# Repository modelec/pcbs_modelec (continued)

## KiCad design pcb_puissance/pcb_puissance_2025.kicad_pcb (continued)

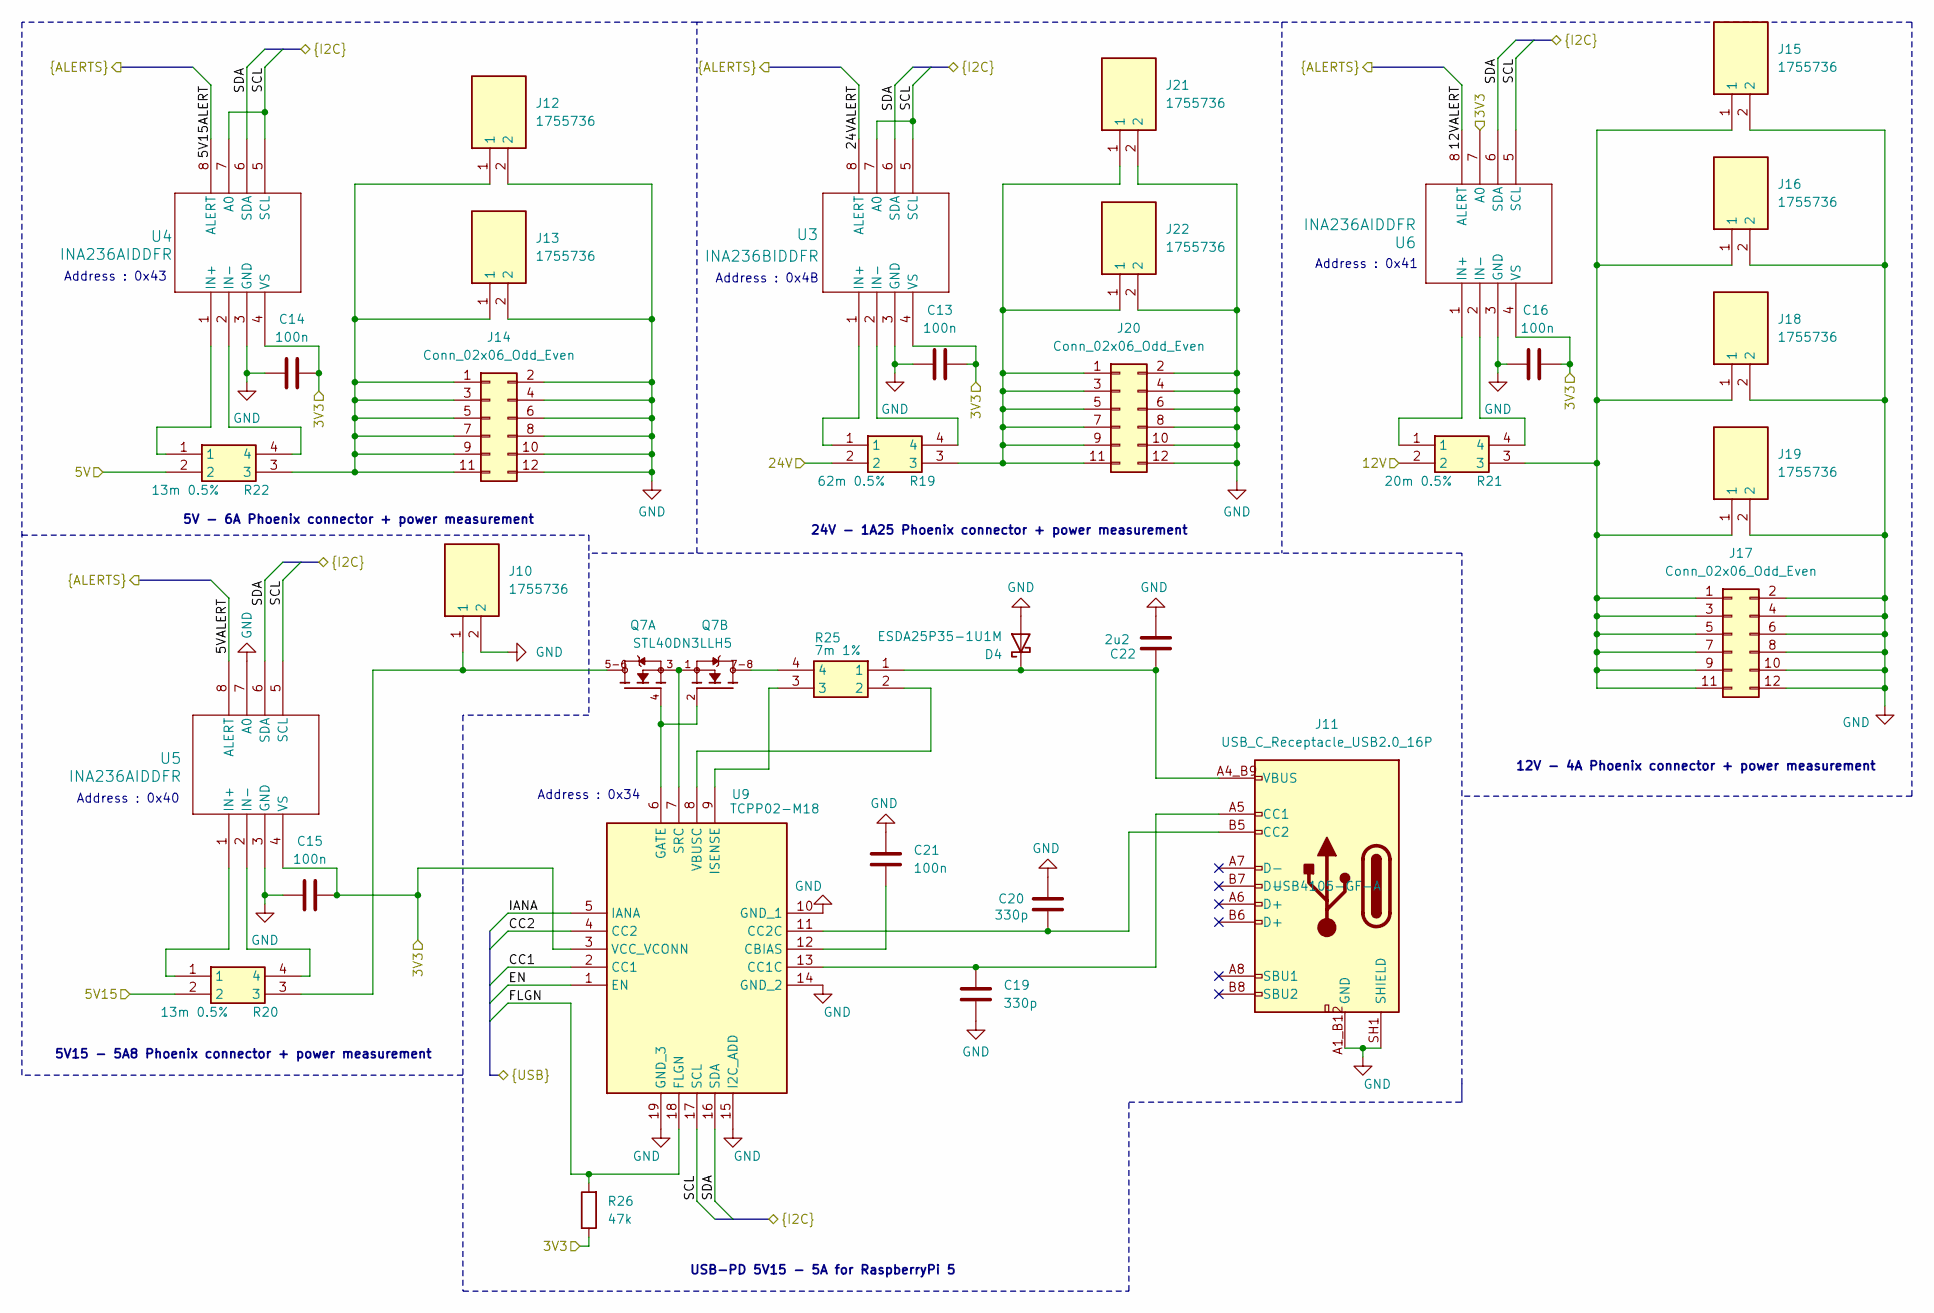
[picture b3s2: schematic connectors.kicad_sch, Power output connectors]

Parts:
C13, C14, C15, C16, C21: 100n; C_0805_2012Metric_Pad1.18x1.45mm_HandSolder; Manufacturer_Part_Number VJ0805Y104KXAMR
C19, C20: 330p; C_0805_2012Metric_Pad1.18x1.45mm_HandSolder; Manufacturer_Part_Number VJ0805A331FXACW1BC
C22: 2u2; C_0805_2012Metric_Pad1.18x1.45mm_HandSolder; Manufacturer_Part_Number VJ0805G225KXQTW1BC
D4: ESDA25P35-1U1M; QFN1610_STM; Manufacturer_Part_Number ESDA25P35-1U1M
J10, J12, J13, J15, J16, J18, J19, J21, J22: 1755736; PhoenixContact_MSTBVA_2,5_2-G-5,08_1x02_P5.08mm_Vertical; Manufacturer_Part_Number 1755736; Mouser Part Number 651-1755736
J11: USB_C_Receptacle_USB2.0_16P; GCT_USB4105-GF-A; Manufacturer_Part_Number USB4105-GF-A
J14, J17, J20: Conn_02x06_Odd_Even; PinHeader_2x06_P1.27mm_Vertical
Q7: STL40DN3LLH5; TRANS_STL40DN3LLH5; PARTREV 7
R19: 62m 0.5%; L4CL1206LR013DNR; Manufacturer_Part_Number L4CL1206LR062DNR
R20, R22: 13m 0.5%; L4CL1206LR013DNR; Manufacturer_Part_Number L4CL1206LR013DNR
R21: 20m 0.5%; L4CL1206LR013DNR; Manufacturer_Part_Number L4CL1206LR020DNR
R25: 7m 1%; L4CL1206LR013DNR; Manufacturer_Part_Number L4CL1206LR007FNR
R26: 47k; R_0805_2012Metric_Pad1.20x1.40mm_HandSolder; Manufacturer_Part_Number CRCW080547K0FKEA
U3: INA236BIDDFR; SOT23-8_DDF_TEX; Manufacturer_Part_Number INA236BIDDFR
U4, U5, U6: INA236AIDDFR; SOT23-8_DDF_TEX; Manufacturer_Part_Number INA236AIDDFR
U9: TCPP02-M18; QFN50P350X350X60-19N-D; Mouser Part Number 511-TCPP02-M18

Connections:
/3V3: C13.2, C14.2, C15.2, C16.2, R26.1, U3.4 (VS), U4.4 (VS), U5.4 (VS), U6.4 (VS), U6.7 (A0), U9.3 (VCC_VCONN); also elsewhere on the board
/Converters/5V: R22.2; also elsewhere on the board
/Converters/5V15: R20.2; also elsewhere on the board
/Converters/12V: R21.2; also elsewhere on the board
/Converters/24V: R19.2; also elsewhere on the board
/Microcontroller/12VALERT: U3.8 (ALERT), U4.8 (ALERT), U5.8 (ALERT), U6.8 (ALERT); also elsewhere on the board
/Microcontroller/CC1: U9.2 (CC1); also elsewhere on the board
/Microcontroller/CC2: U9.4 (CC2); also elsewhere on the board
/Microcontroller/EN: U9.1 (EN)
/Microcontroller/FLGN: R26.2, U9.18 (FLGN); also elsewhere on the board
/Microcontroller/IANA: U9.5 (IANA)
/Microcontroller/SCL: U3.5 (SCL), U3.7 (A0), U4.5 (SCL), U4.7 (A0), U5.5 (SCL), U6.5 (SCL), U9.17 (SCL); also elsewhere on the board
/Microcontroller/SDA: U3.6 (SDA), U4.6 (SDA), U5.6 (SDA), U6.6 (SDA), U9.16 (SDA); also elsewhere on the board
GND: C13.1, C14.1, C15.1, C16.1, C19.2, C20.1, C21.1, C22.2, D4.2 (A), J10.2, J11.A1_B12 (GND), J11.B1_A12 (GND), J11.SH1 (SHIELD), J11.SH2, J11.SH3, J11.SH4, J12.2, J13.2, J14.2, J14.4, J14.6, J14.8, J14.10, J14.12, J15.2, J16.2, J17.2, J17.4, J17.6, J17.8, J17.10, J17.12, J18.2, J19.2, J20.2, J20.4, J20.6, J20.8, J20.10, J20.12, J21.2, J22.2, U3.3 (GND), U4.3 (GND), U5.3 (GND), U5.7 (A0), U6.3 (GND), U9.10 (GND_1), U9.14 (GND_2), U9.15 (I2C_ADD), U9.19 (GND_3); also elsewhere on the board
unnamed: C22.1, D4.1 (K), J11.A4_B9 (VBUS), J11.B4_A9 (VBUS), R25.1
unnamed: J10.1, Q7.5-6, R20.3
unnamed: C19.1, J11.A5 (CC1), U9.13 (CC1C)
unnamed: C20.2, J11.B5 (CC2), U9.11 (CC2C)
unnamed: J12.1, J13.1, J14.1, J14.3, J14.5, J14.7, J14.9, J14.11, R22.3
unnamed: J15.1, J16.1, J17.1, J17.3, J17.5, J17.7, J17.9, J17.11, J18.1, J19.1, R21.3
unnamed: J20.1, J20.3, J20.5, J20.7, J20.9, J20.11, J21.1, J22.1, R19.3
unnamed: Q7.7-8, R25.4
unnamed: R19.1, U3.1 (IN+)
unnamed: R19.4, U3.2 (IN-)
unnamed: R22.1, U4.1 (IN+)
unnamed: R22.4, U4.2 (IN-)
unnamed: R20.1, U5.1 (IN+)
unnamed: R20.4, U5.2 (IN-)
unnamed: R21.1, U6.1 (IN+)
unnamed: R21.4, U6.2 (IN-)
unnamed: C21.2, U9.12 (CBIAS)
unnamed: Q7.2, Q7.4, U9.6 (GATE)
unnamed: R25.3, U9.9 (ISENSE)
unnamed: Q7.1, Q7.3, U9.7 (SRC)
unnamed: R25.2, U9.8 (VBUSC)

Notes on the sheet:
Address : 0x41
5V15 - 5A8 Phoenix connector + power measurement
5V - 6A Phoenix connector + power measurement
Address : 0x43
USB-PD 5V15 - 5A for RaspberryPi 5
Address : 0x34
Address : 0x4B
24V - 1A25 Phoenix connector + power measurement
12V - 4A Phoenix connector + power measurement
Address : 0x40

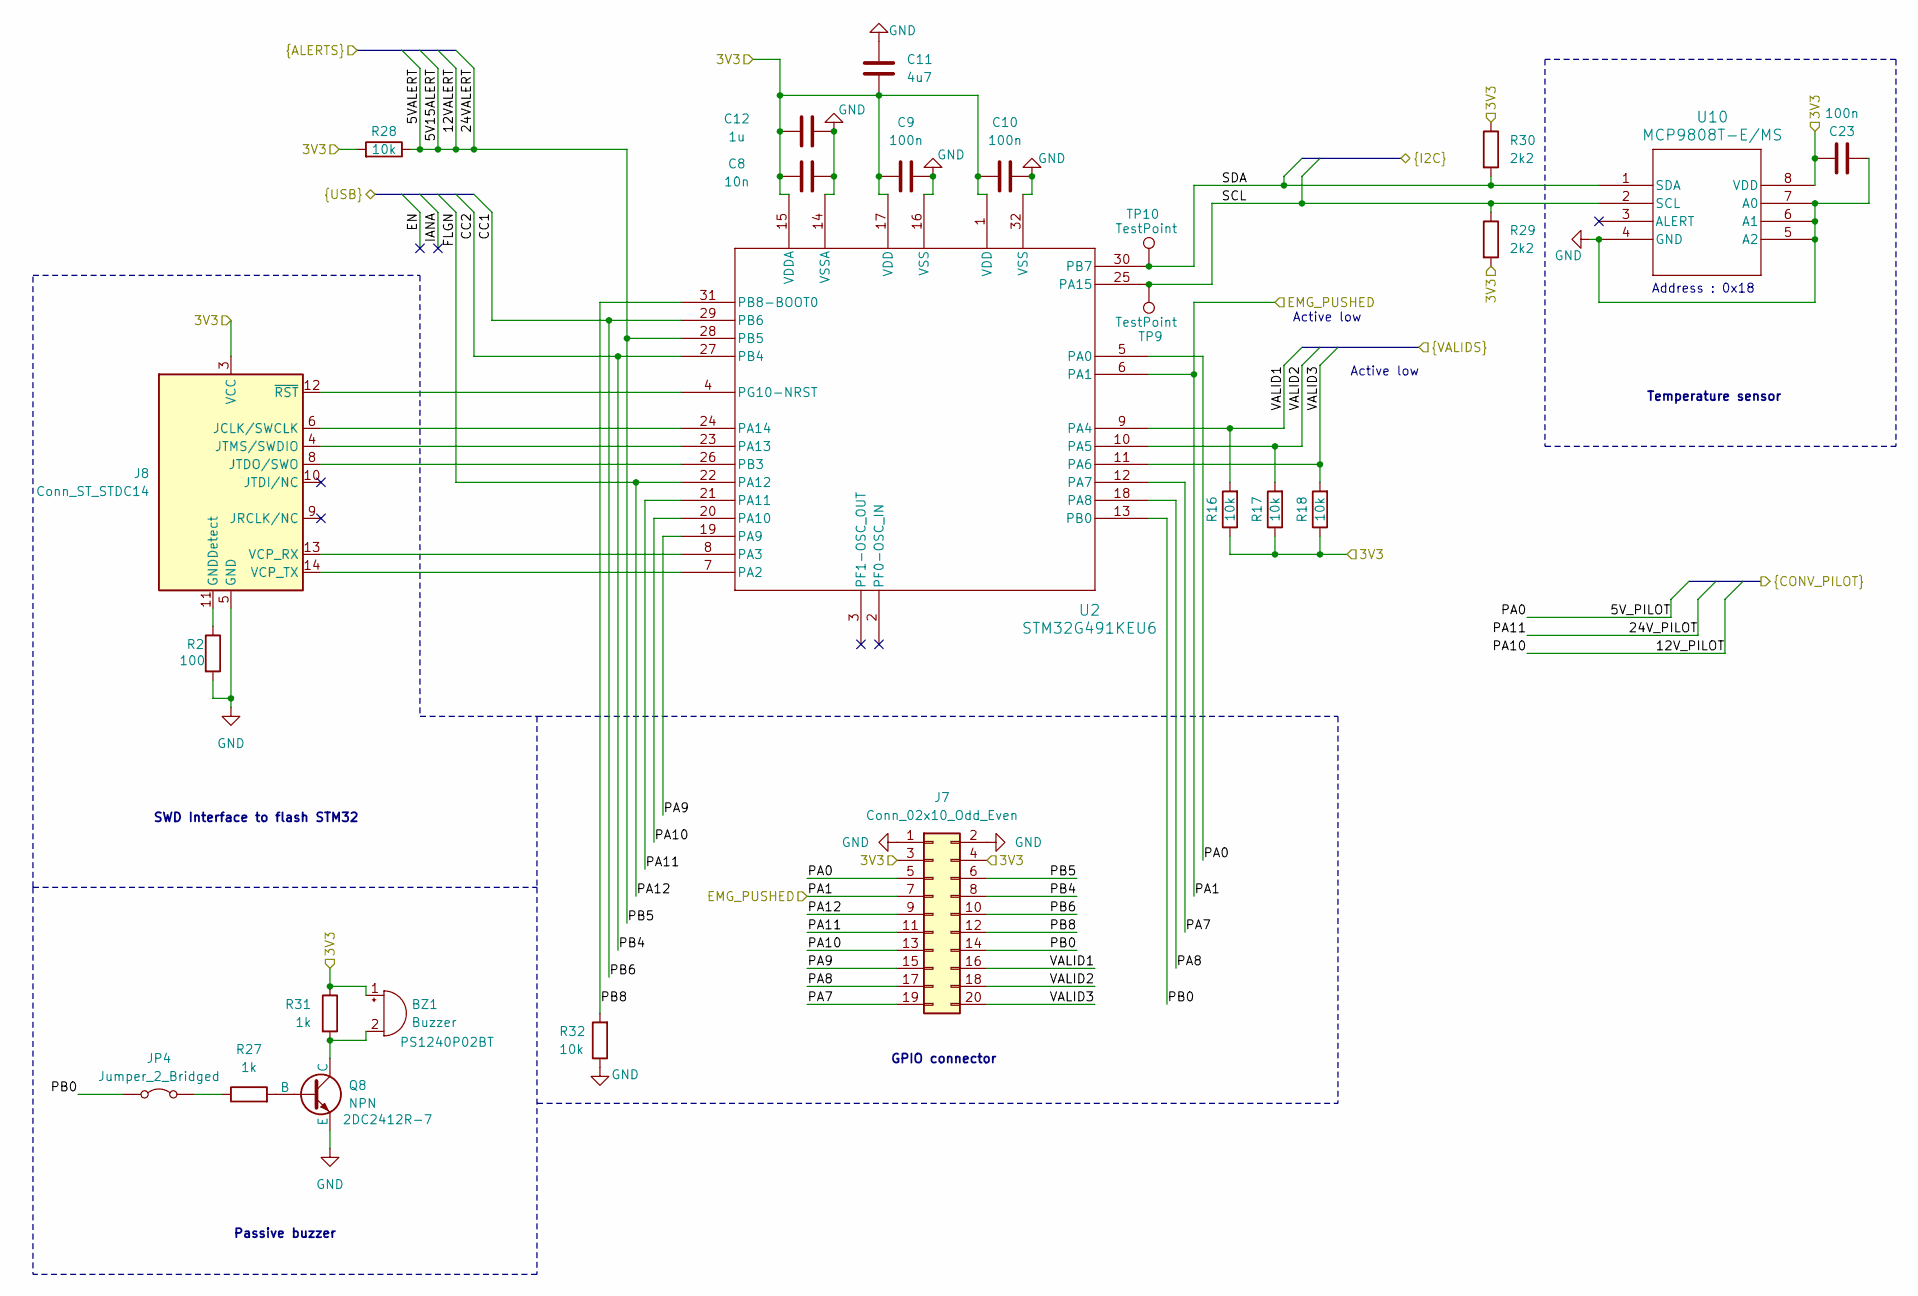
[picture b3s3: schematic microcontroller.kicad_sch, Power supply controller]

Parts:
BZ1: Buzzer; XTAL_PS1240P02BT_TDK; Manufacturer_Part_Number PS1240P02BT
C8: 10n; C_0805_2012Metric_Pad1.18x1.45mm_HandSolder; Manufacturer_Part_Number VJ0805Y103KXAMC
C9, C10, C23: 100n; C_0805_2012Metric_Pad1.18x1.45mm_HandSolder; Manufacturer_Part_Number VJ0805Y104KXAMR
C11: 4u7; C_0805_2012Metric_Pad1.18x1.45mm_HandSolder; Manufacturer_Part_Number VJ0805G475KXQTW1BC
C12: 1u; C_0805_2012Metric_Pad1.18x1.45mm_HandSolder; Manufacturer_Part_Number VJ0805Y105KXQTW1BC
J7: Conn_02x10_Odd_Even; PinHeader_2x10_P1.27mm_Vertical
J8: Conn_ST_STDC14; PinHeader_2x07_P1.27mm_Vertical; Manufacturer_Part_Number 3220-14-0100-00
JP4: Jumper_2_Bridged; PinHeader_1x02_P1.27mm_Vertical
Q8: NPN; SOT-23; Manufacturer_Part_Number 2DC2412R-7
R2: 100; R_0805_2012Metric_Pad1.20x1.40mm_HandSolder; Manufacturer_Part_Number CRCW0805100RFKEA
R16, R17, R18, R28, R32: 10k; R_0805_2012Metric_Pad1.20x1.40mm_HandSolder; Manufacturer_Part_Number CRCW080510K0FKEA
R27, R31: 1k; R_0805_2012Metric_Pad1.20x1.40mm_HandSolder; Manufacturer_Part_Number CRCW08051K00FKEA
R29, R30: 2k2; R_0805_2012Metric_Pad1.20x1.40mm_HandSolder; Manufacturer_Part_Number CRCW08052K20FKEA
TP9, TP10: TestPoint; TestPoint_Bridge_Pitch2.0mm_Drill0.7mm
U2: STM32G491KEU6
U10: MCP9808T-E/MS; MSOP8_MC_MCH; Manufacturer_Part_Number MCP9808T-E/MS

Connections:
/3V3: BZ1.1 (+), C8.1, C9.1, C10.1, C11.1, C12.1, C23.2, J7.3, J7.4, J8.3 (VCC), R16.1, R17.1, R18.1, R28.2, R29.2, R30.1, R31.1, U2.1 (VDD), U2.15 (VDDA), U2.17 (VDD), U10.8 (VDD); also elsewhere on the board
/Converters/5V_PILOT: J7.5, U2.5 (PA0); also elsewhere on the board
/Converters/12V_PILOT: J7.13, U2.20 (PA10); also elsewhere on the board
/Converters/24V_PILOT: J7.11, U2.21 (PA11); also elsewhere on the board
/Microcontroller/12VALERT: J7.6, R28.1, U2.28 (PB5); also elsewhere on the board
/Microcontroller/CC1: J7.10, U2.29 (PB6); also elsewhere on the board
/Microcontroller/CC2: J7.8, U2.27 (PB4); also elsewhere on the board
/Microcontroller/FLGN: J7.9, U2.22 (PA12); also elsewhere on the board
/Microcontroller/PA1: J7.7, U2.6 (PA1); also elsewhere on the board
/Microcontroller/PA7: J7.19, U2.12 (PA7)
/Microcontroller/PA8: J7.17, U2.18 (PA8)
/Microcontroller/PA9: J7.15, U2.19 (PA9)
/Microcontroller/PB0: J7.14, JP4.1 (A), U2.13 (PB0)
/Microcontroller/PB8: J7.12, R32.2, U2.31 (PB8-BOOT0)
/Microcontroller/SCL: R29.1, TP9.1, U2.25 (PA15), U10.2 (SCL); also elsewhere on the board
/Microcontroller/SDA: R30.2, TP10.1, U2.30 (PB7), U10.1 (SDA); also elsewhere on the board
/Microcontroller/VALID1: J7.16, R16.2, U2.9 (PA4); also elsewhere on the board
/Microcontroller/VALID2: J7.18, R17.2, U2.10 (PA5); also elsewhere on the board
/Microcontroller/VALID3: J7.20, R18.2, U2.11 (PA6); also elsewhere on the board
GND: C8.2, C9.2, C10.2, C11.2, C12.2, C23.1, J7.1, J7.2, J8.5 (GND), J8.7 (GND), Q8.1 (E), R2.2, R32.1, U2.14 (VSSA), U2.16 (VSS), U2.32 (VSS), U10.4 (GND), U10.5 (A2), U10.6 (A1), U10.7 (A0); also elsewhere on the board
unnamed: BZ1.2 (-), Q8.3 (C), R31.2
unnamed: J8.11 (GNDDetect), R2.1
unnamed: J8.6 (JCLK/SWCLK), U2.24 (PA14)
unnamed: J8.8 (JTDO/SWO), U2.26 (PB3)
unnamed: J8.4 (JTMS/SWDIO), U2.23 (PA13)
unnamed: J8.13 (VCP_RX), U2.8 (PA3)
unnamed: J8.14 (VCP_TX), U2.7 (PA2)
unnamed: J8.12 (~RST), U2.4 (PG10-NRST)
unnamed: JP4.2 (B), R27.1
unnamed: Q8.2 (B), R27.2

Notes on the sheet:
Active low
GPIO connector
Passive buzzer
SWD Interface to flash STM32
Temperature sensor
Address : 0x18

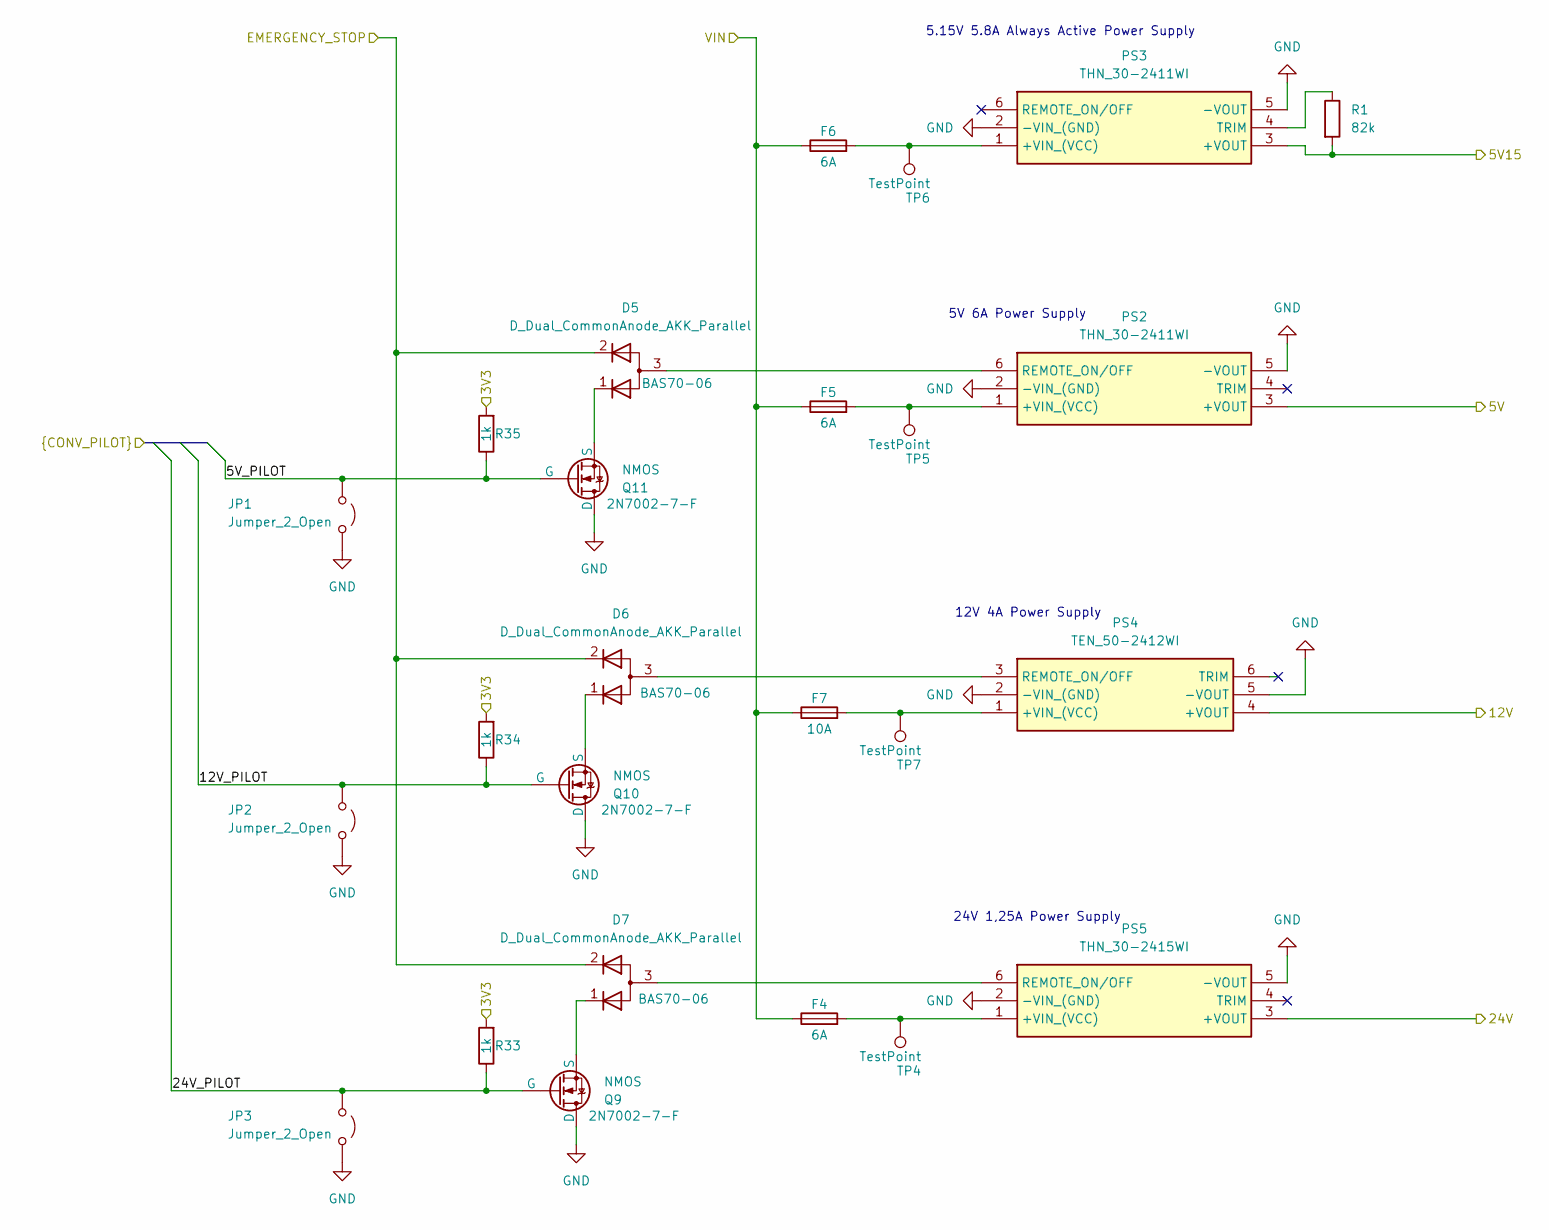
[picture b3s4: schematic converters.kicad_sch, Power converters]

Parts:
D5, D6, D7: D_Dual_CommonAnode_AKK_Parallel; TSOT-23_HandSoldering; Manufacturer_Part_Number BAS70-06
F4, F5, F6: 6A; 01550900M; Manufacturer_Part_Number 01550900M
F7: 10A; 01550900M; Manufacturer_Part_Number 01550900M
JP1, JP2, JP3: Jumper_2_Open; PinHeader_1x02_P1.27mm_Vertical
PS2, PS3: THN_30-2411WI; THN301211; Manufacturer_Part_Number THN_30-2411WI; Mouser Part Number 495-THN-30-1211
PS4: TEN_50-2412WI; TEN_50-2411; Manufacturer_Part_Number TEN_50-2412WI; Mouser Part Number 495-TEN50-2412WI
PS5: THN_30-2415WI; THN301211; Manufacturer_Part_Number THN_30-2415WI; Mouser Part Number 495-THN-30-1211
Q9, Q10, Q11: NMOS; SOT-23; Manufacturer_Part_Number 2N7002-7-F
R1: 82k; R_0805_2012Metric_Pad1.20x1.40mm_HandSolder; Manufacturer_Part_Number CRCW080582K0FKEA
R33, R34, R35: 1k; R_0805_2012Metric_Pad1.20x1.40mm_HandSolder; Manufacturer_Part_Number CRCW08051K00FKEA
TP4, TP5, TP6, TP7: TestPoint; TestPoint_Pad_D1.5mm

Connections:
/3V3: R33.2, R34.2, R35.2; also elsewhere on the board
/Converters/5V: PS2.3 (+VOUT); also elsewhere on the board
/Converters/5V15: PS3.3 (+VOUT), R1.2; also elsewhere on the board
/Converters/5V_PILOT: JP1.1 (A), Q11.2 (G), R35.1; also elsewhere on the board
/Converters/12V: PS4.4 (+VOUT); also elsewhere on the board
/Converters/12V_PILOT: JP2.1 (A), Q10.2 (G), R34.1; also elsewhere on the board
/Converters/24V: PS5.3 (+VOUT); also elsewhere on the board
/Converters/24V_PILOT: JP3.1 (A), Q9.2 (G), R33.1; also elsewhere on the board
/Converters/EMERGENCY_STOP: D5.2 (K), D6.2 (K), D7.2 (K); also elsewhere on the board
/Converters/VIN: F4.1, F5.1, F6.1, F7.1; also elsewhere on the board
GND: JP1.2 (B), JP2.2 (B), JP3.2 (B), PS2.2 (-VIN_(GND)), PS2.5 (-VOUT), PS3.2 (-VIN_(GND)), PS3.5 (-VOUT), PS4.2 (-VIN_(GND)), PS4.5 (-VOUT), PS5.2 (-VIN_(GND)), PS5.5 (-VOUT), Q9.3 (D), Q10.3 (D), Q11.3 (D); also elsewhere on the board
unnamed: D5.3 (A), PS2.6 (REMOTE_ON/OFF)
unnamed: D6.3 (A), PS4.3 (REMOTE_ON/OFF)
unnamed: D7.3 (A), PS5.6 (REMOTE_ON/OFF)
unnamed: F5.2, PS2.1 (+VIN_(VCC)), TP5.1
unnamed: F6.2, PS3.1 (+VIN_(VCC)), TP6.1
unnamed: PS3.4 (TRIM), R1.1
unnamed: F7.2, PS4.1 (+VIN_(VCC)), TP7.1
unnamed: F4.2, PS5.1 (+VIN_(VCC)), TP4.1
unnamed: D7.1 (K), Q9.1 (S)
unnamed: D6.1 (K), Q10.1 (S)
unnamed: D5.1 (K), Q11.1 (S)

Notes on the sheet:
24V 1,25A Power Supply
12V 4A Power Supply
5V 6A Power Supply
5.15V 5.8A Always Active Power Supply

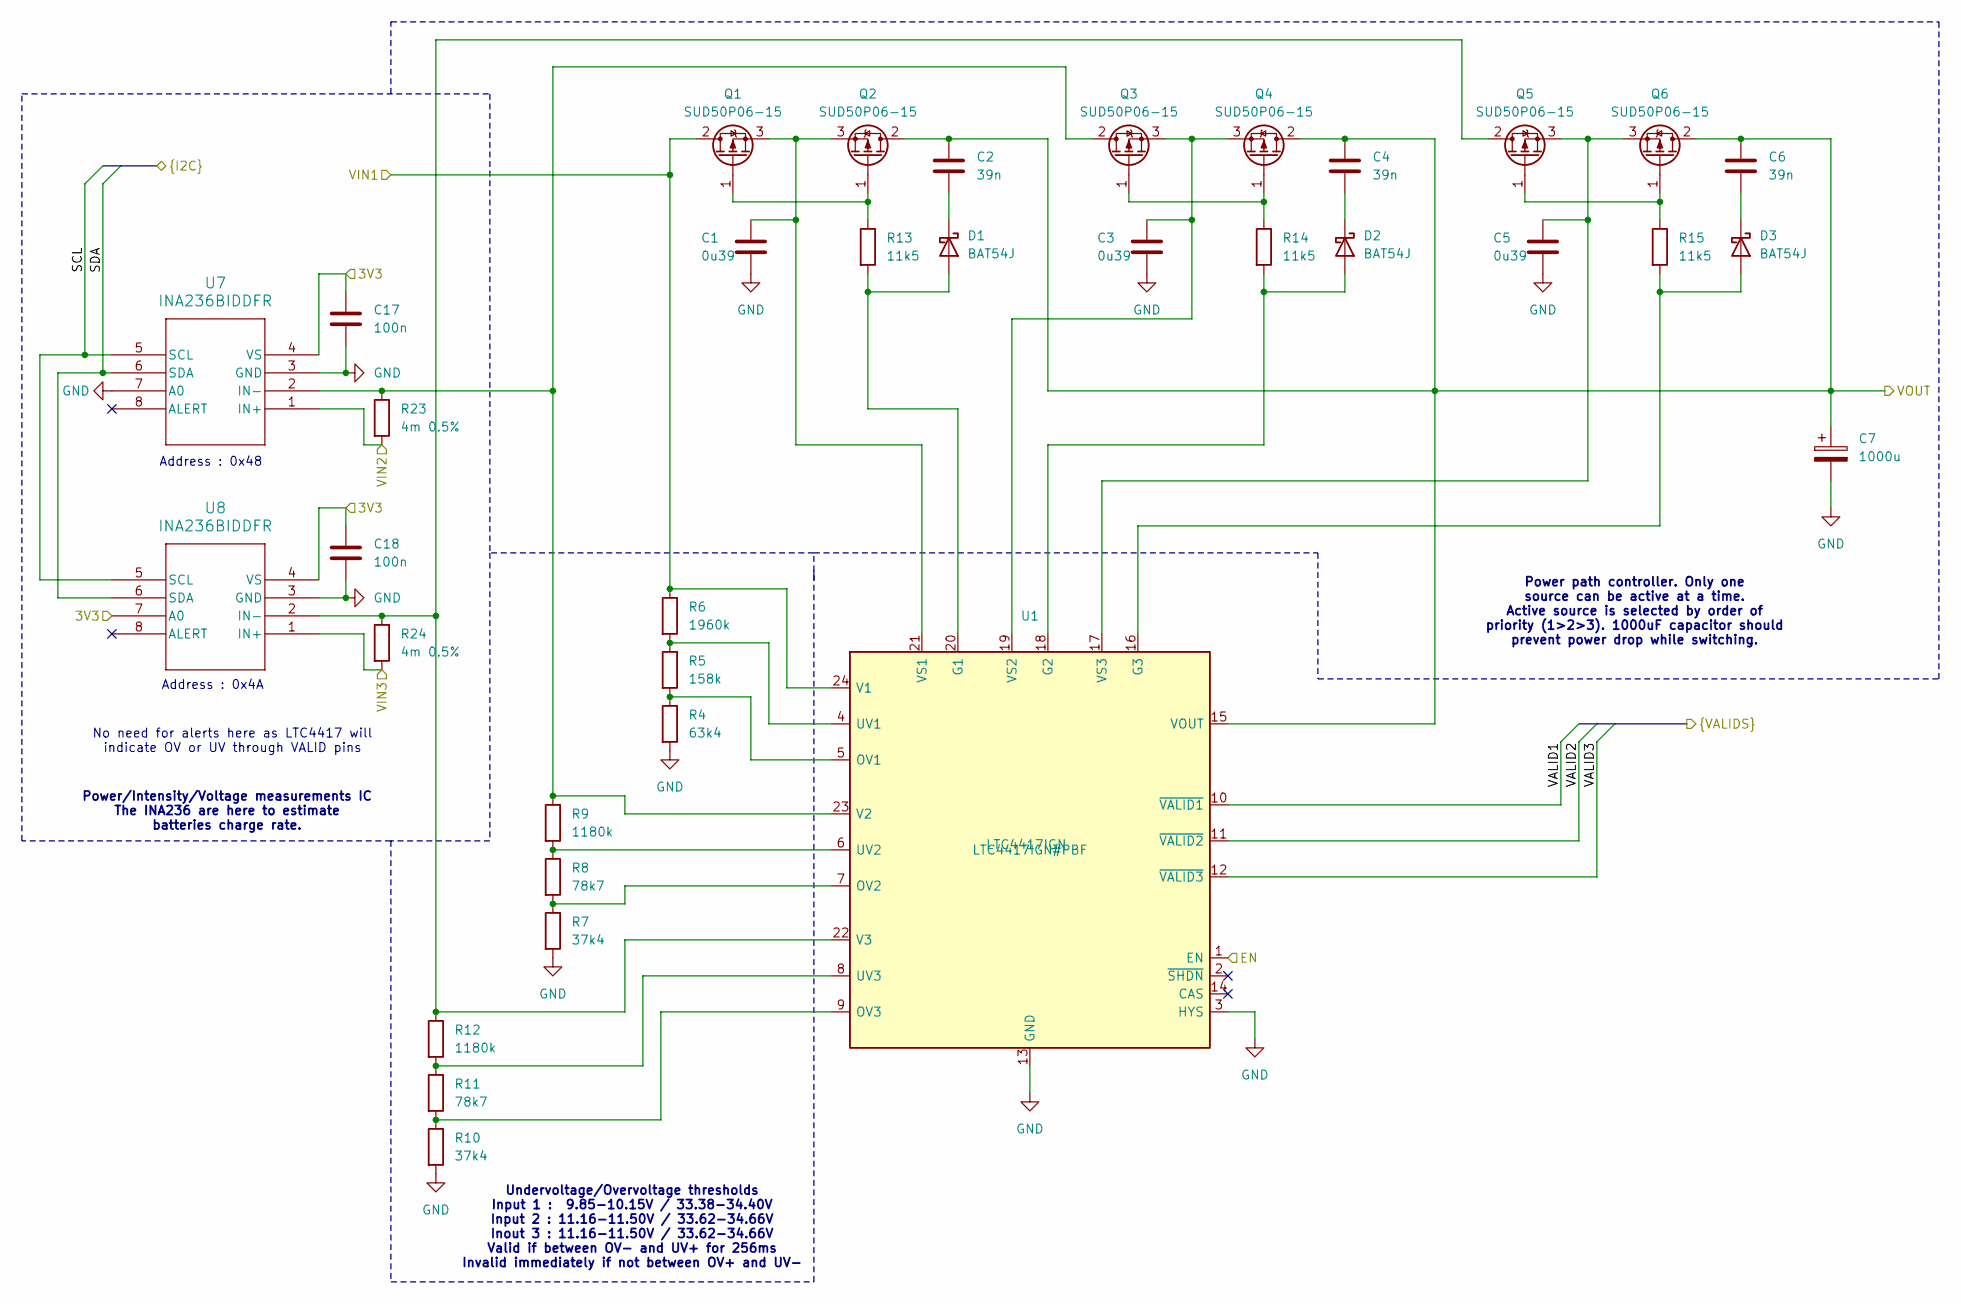
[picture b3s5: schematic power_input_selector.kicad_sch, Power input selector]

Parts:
C1, C3, C5: 0u39; C_0805_2012Metric_Pad1.18x1.45mm_HandSolder; Manufacturer_Part_Number C0805C394K5RACTU
C2, C4, C6: 39n; C_0805_2012Metric_Pad1.18x1.45mm_HandSolder; Manufacturer_Part_Number VJ0805Y393KXAAC
C7: 1000u; CP_Radial_D13.0mm_P5.00mm; Manufacturer_Part_Number UVY1H102MHD
C17, C18: 100n; C_0805_2012Metric_Pad1.18x1.45mm_HandSolder; Manufacturer_Part_Number VJ0805Y104KXAMR
D1, D2, D3: BAT54J; D_SOD-323F; Manufacturer_Part_Number BAT54J
Q1, Q2, Q3, Q4, Q5, Q6: SUD50P06-15; TO-252-2; Manufacturer_Part_Number SUD50P06-15-BE3
R4: 63k4; R_0805_2012Metric_Pad1.20x1.40mm_HandSolder; Manufacturer_Part_Number CRCW080563K4FKEA
R5: 158k; R_0805_2012Metric_Pad1.20x1.40mm_HandSolder
R6: 1960k; R_0805_2012Metric_Pad1.20x1.40mm_HandSolder; Manufacturer_Part_Number CRCW08051M96FKEA
R7, R10: 37k4; R_0805_2012Metric_Pad1.20x1.40mm_HandSolder; Manufacturer_Part_Number CRCW080537K4FKEA
R8, R11: 78k7; R_0805_2012Metric_Pad1.20x1.40mm_HandSolder; Manufacturer_Part_Number CRCW080578K7FKEA
R9, R12: 1180k; R_0805_2012Metric_Pad1.20x1.40mm_HandSolder; Manufacturer_Part_Number CRCW08051M18FKEA
R13, R14, R15: 11k5; R_0805_2012Metric_Pad1.20x1.40mm_HandSolder; Manufacturer_Part_Number CRCW080511K5FKEA
R23, R24: 4m 0.5%; R_2512_6332Metric_Pad1.40x3.35mm_HandSolder; Manufacturer_Part_Number PEWF2512D4L00Q9
U1: LTC4417IGN; SSOP-24_3.9x8.7mm_P0.635mm; Manufacturer_Part_Number LTC4417IGN#PBF
U7, U8: INA236BIDDFR; SOT23-8_DDF_TEX; Manufacturer_Part_Number INA236BIDDFR

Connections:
/3V3: C17.1, C18.1, U7.4 (VS), U8.4 (VS), U8.7 (A0); also elsewhere on the board
/Converters/VIN: C2.1, C4.1, C6.1, C7.1, Q2.2 (D), Q4.2 (D), Q6.2 (D), U1.15 (VOUT); also elsewhere on the board
/Microcontroller/SCL: U7.5 (SCL), U8.5 (SCL); also elsewhere on the board
/Microcontroller/SDA: U7.6 (SDA), U8.6 (SDA); also elsewhere on the board
/Microcontroller/VALID1: U1.10 (~VALID1); also elsewhere on the board
/Microcontroller/VALID2: U1.11 (~VALID2); also elsewhere on the board
/Microcontroller/VALID3: U1.12 (~VALID3); also elsewhere on the board
/power_input_selector/EN: U1.1 (EN); also elsewhere on the board
/power_input_selector/VIN1: Q1.2 (D), R6.1, U1.24 (V1); also elsewhere on the board
/power_input_selector/VIN2: R23.2, U7.1 (IN+); also elsewhere on the board
/power_input_selector/VIN3: R24.2, U8.1 (IN+); also elsewhere on the board
GND: C1.2, C3.2, C5.2, C7.2, C17.2, C18.2, R4.2, R7.2, R10.2, U1.3 (HYS), U1.13 (GND), U7.3 (GND), U7.7 (A0), U8.3 (GND); also elsewhere on the board
unnamed: D1.2 (A), R13.2, U1.20 (G1)
unnamed: C2.2, D1.1 (K)
unnamed: D2.2 (A), R14.2, U1.18 (G2)
unnamed: C4.2, D2.1 (K)
unnamed: D3.2 (A), R15.2, U1.16 (G3)
unnamed: C6.2, D3.1 (K)
unnamed: Q1.1 (G), Q2.1 (G), R13.1
unnamed: C1.1, Q1.3 (S), Q2.3 (S), U1.21 (VS1)
unnamed: Q3.2 (D), R9.1, R23.1, U1.23 (V2), U7.2 (IN-)
unnamed: Q3.1 (G), Q4.1 (G), R14.1
unnamed: C3.1, Q3.3 (S), Q4.3 (S), U1.19 (VS2)
unnamed: Q5.2 (D), R12.1, R24.1, U1.22 (V3), U8.2 (IN-)
unnamed: Q5.1 (G), Q6.1 (G), R15.1
unnamed: C5.1, Q5.3 (S), Q6.3 (S), U1.17 (VS3)
unnamed: R4.1, R5.2, U1.5 (OV1)
unnamed: R7.1, R8.2, U1.7 (OV2)
unnamed: R10.1, R11.2, U1.9 (OV3)
unnamed: R5.1, R6.2, U1.4 (UV1)
unnamed: R8.1, R9.2, U1.6 (UV2)
unnamed: R11.1, R12.2, U1.8 (UV3)

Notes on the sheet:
Address : 0x4A
Undervoltage/Overvoltage thresholds Input 1 : 9.85-10.15V / 33.38-34.40V Input 2 : 11.16-11.50V / 33.62-34.66V Inout 3 : 11.16-11.50V / 33.62-34.66V Valid if between OV- and UV+ for 256ms Invalid immediately if not between OV+ and UV-
No need for alerts here as LTC4417 will indicate OV or UV through VALID pins
Power/Intensity/Voltage measurements IC The INA236 are here to estimate batteries charge rate.
Address : 0x48
Power path controller. Only one source can be active at a time. Active source is selected by order of priority (1>2>3). 1000uF capacitor should prevent power drop while switching.

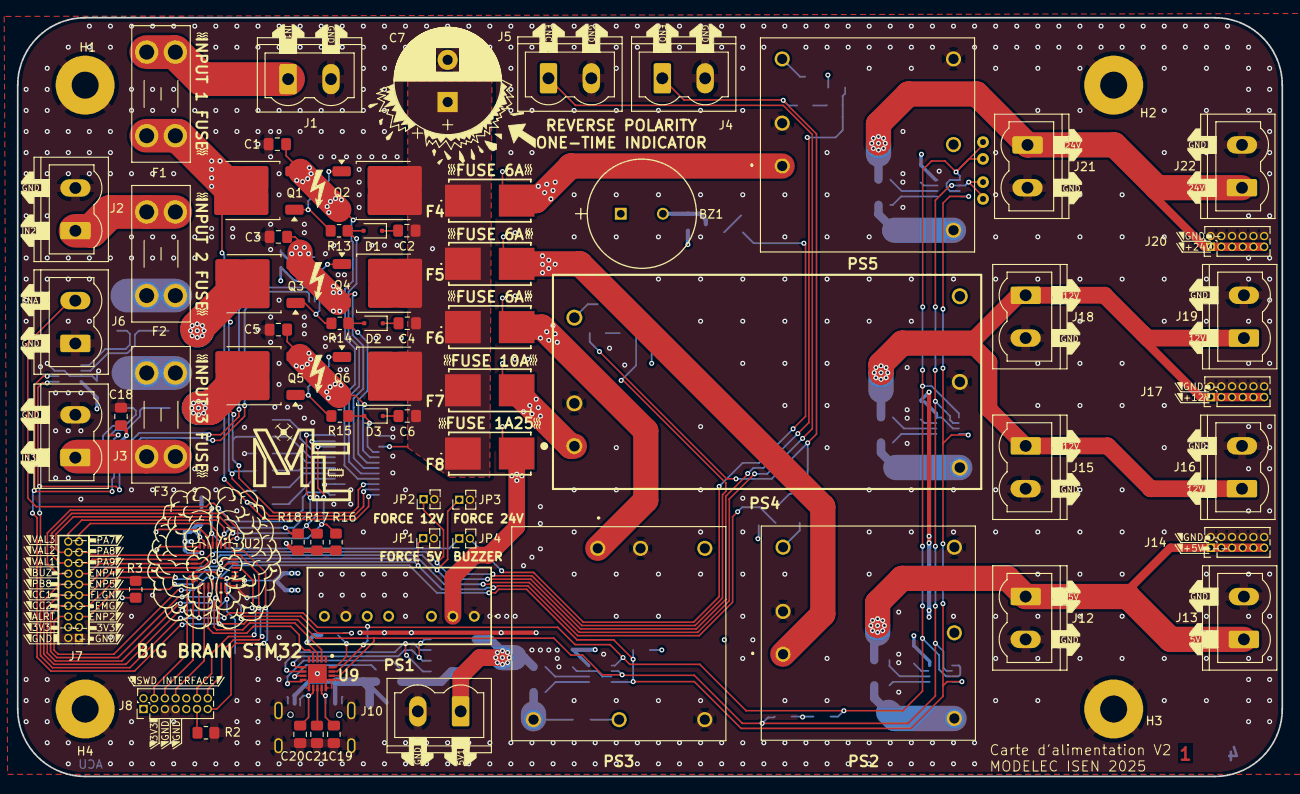
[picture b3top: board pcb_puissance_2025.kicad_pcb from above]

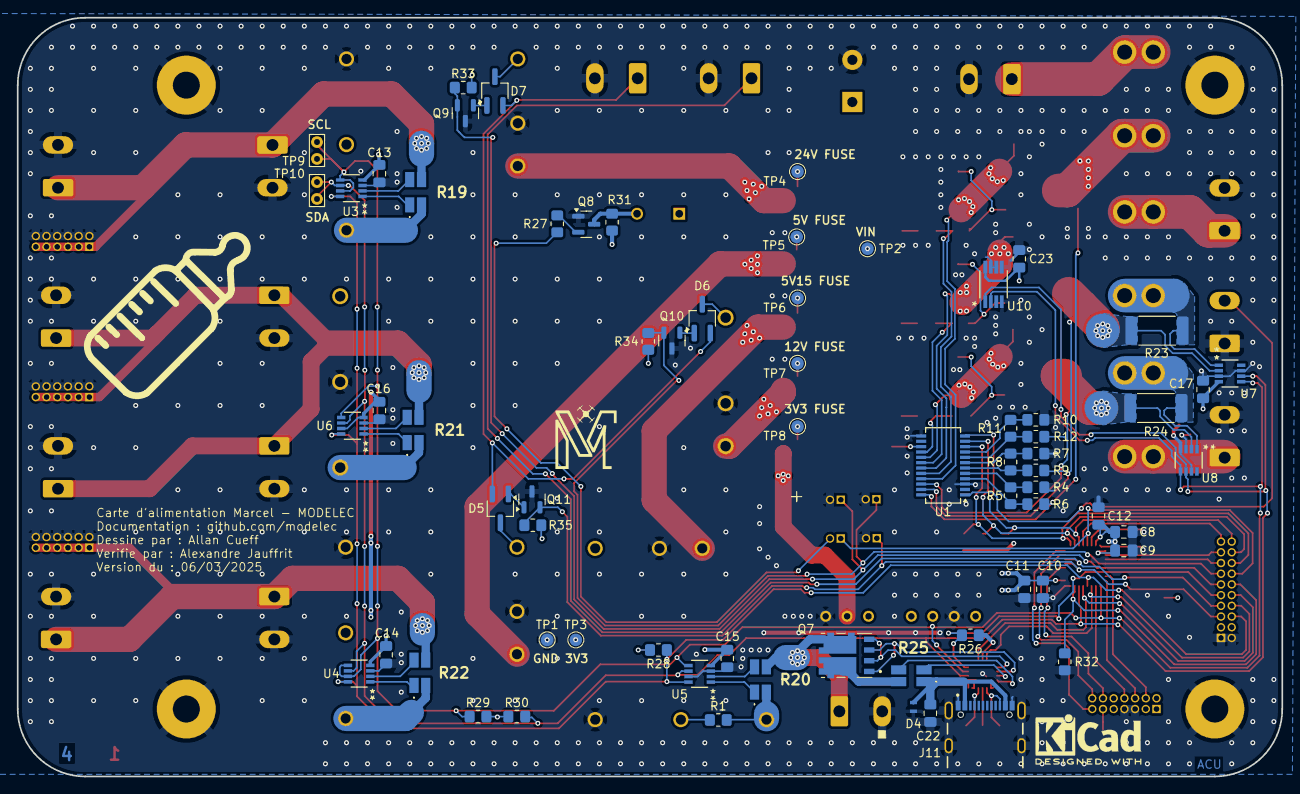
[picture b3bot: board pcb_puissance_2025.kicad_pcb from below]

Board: 4 copper layers, 150.0 x 90.0 mm, 139 parts (67 on the bottom side), 96 nets.
